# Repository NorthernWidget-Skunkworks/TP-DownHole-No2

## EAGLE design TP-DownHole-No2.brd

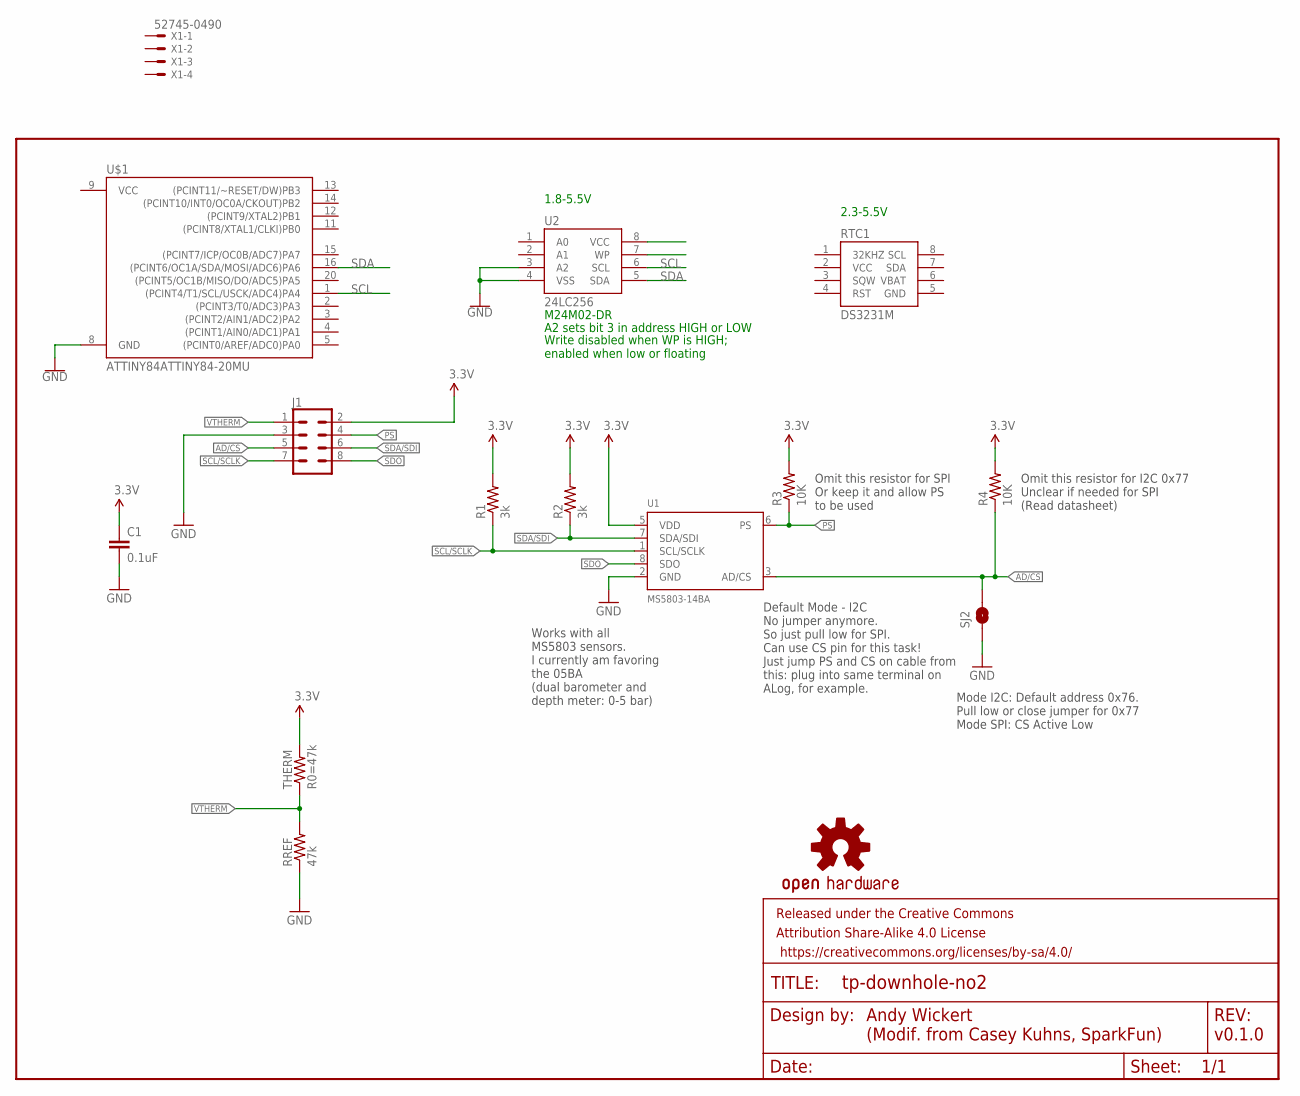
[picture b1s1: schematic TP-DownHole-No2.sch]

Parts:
C1: 0.1uF; 0603-CAP
FRAME1: FRAME-LETTER; CREATIVE_COMMONS
J1: CONN_04X2; 2X4
LOGO3: OSHW-LOGOS; OSHW-LOGO-S
R1, R2: 3k; 0603-RES
R3, R4: 10K; 0603-RES
RREF: 47k; R0603
RTC1: DS3231M; SO08
SJ2: I2C-select; SJ_2S-NO
THERM: R0=47k; R0603
U1: MS5803-14BA; MS5803
U2: 24LC256; SO08
U$1: ATTINY84ATTINY84-20MU; QFN20
X1: 52745-0490

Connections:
3.3V: C1.1, J1.2, R1.2, R2.2, R3.2, R4.2, THERM.2, U1.5 (VDD)
AD/CS: J1.5, R4.1, SJ2.2, U1.3 (AD/CS)
GND: C1.2, J1.3, RREF.1, RTC1.5 (GND), SJ2.1, U1.2 (GND), U2.3 (A2), U2.4 (VSS), U$1.8 (GND)
PS: J1.4, R3.1, U1.6 (PS)
SCL: U2.6 (SCL), U$1.1 ((PCINT4/T1/SCL/USCK/ADC4)PA4)
SCL/SCLK: J1.7, R1.1, U1.1 (SCL/SCLK)
SDA: U2.5 (SDA), U$1.16 ((PCINT6/OC1A/SDA/MOSI/ADC6)PA6)
SDA/SDI: J1.6, R2.1, U1.7 (SDA/SDI)
SDO: J1.8, U1.8 (SDO)
VBAT: RTC1.6 (VBAT)
VCC: RTC1.2 (VCC)
VTHERM: J1.1, RREF.2, THERM.1
WC: U2.7 (WP)

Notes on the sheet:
Andy Wickert (Modif. from Casey Kuhns, SparkFun)
v0.1.0
Default Mode - I2C No jumper anymore. So just pull low for SPI. Can use CS pin for this task! Just jump PS and CS on cable from this: plug into same terminal on ALog, for example.
Mode I2C: Default address 0x76. Pull low or close jumper for 0x77 Mode SPI: CS Active Low
Omit this resistor for SPI Or keep it and allow PS to be used
Omit this resistor for I2C 0x77 Unclear if needed for SPI (Read datasheet)
Works with all MS5803 sensors. I currently am favoring the 05BA (dual barometer and depth meter: 0-5 bar)
M24M02-DR
A2 sets bit 3 in address HIGH or LOW
Write disabled when WP is HIGH; enabled when low or floating
1.8-5.5V
2.3-5.5V

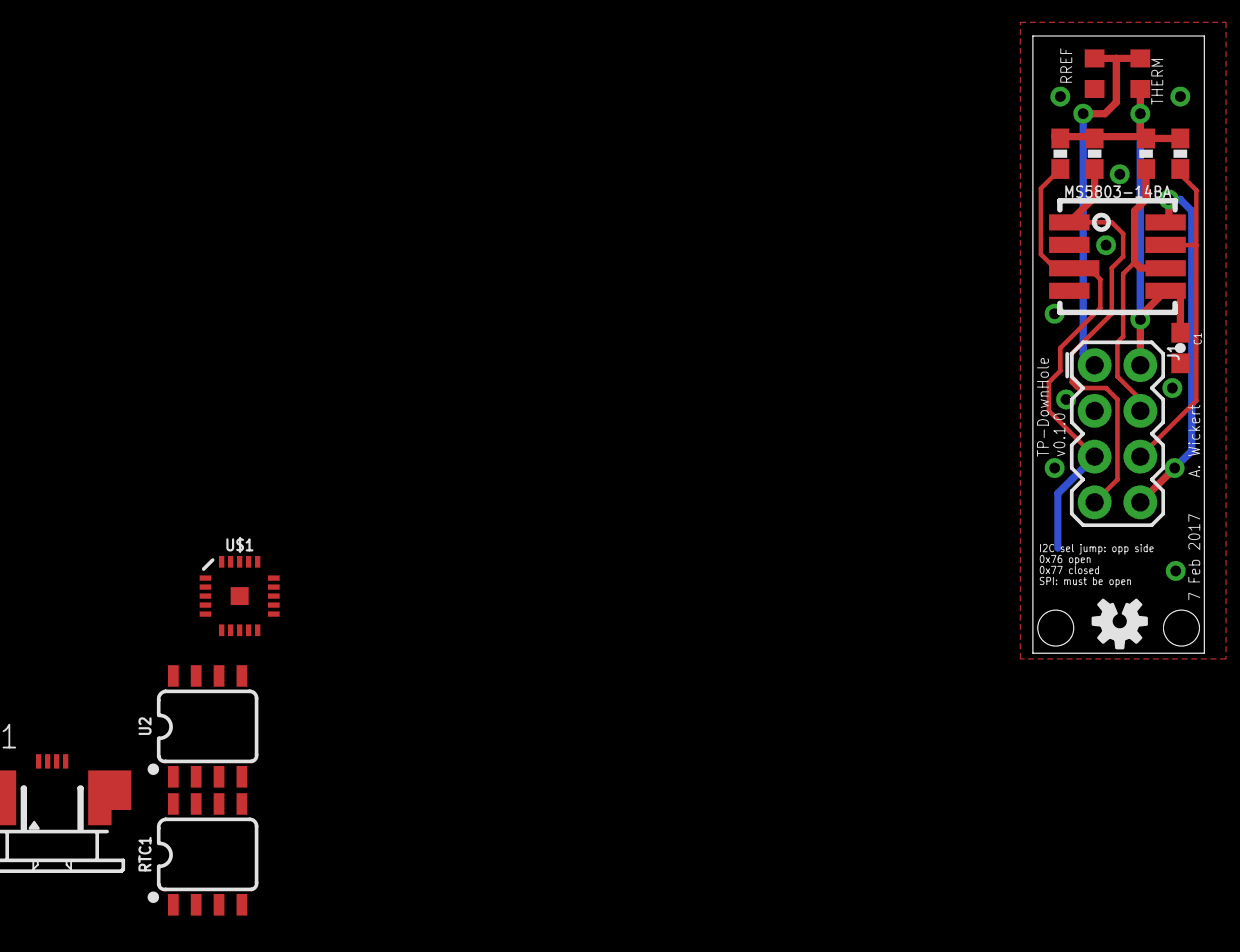
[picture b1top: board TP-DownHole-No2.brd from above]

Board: 2 copper layers, 9.5 x 34.3 mm, 16 parts (1 on the bottom side), 10 nets.

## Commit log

2017-07-28 Local logger
2017-07-28 Added alternative prelim design and calculations
    Added a preliminary design for using the ATTINY441, AT24C512C for an EEPROM, the TPS79718 for a voltage regulator, and the DS1337 as a new RTC
2018-06-17 CC-BY-SA

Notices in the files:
parts and their libraries:
SparkFun-Aesthetics: Licensing: Creative Commons ShareAlike 4.0 International - https://creativecommons.org/licenses/by-sa/4.0
SparkFun-Aesthetics: Released under the Creative Commons Attribution Share-Alike 4.0 License
SparkFun-Aesthetics: https://creativecommons.org/licenses/by-sa/4.0
